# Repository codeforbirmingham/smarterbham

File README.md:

# SmarterBham
The SmarterBham project

# Project Structure
* /citysensor - all the code that runs on the device
* /doc - our documentation.  Requirements, wireframes, flow, security audits, etc
* /web - the web application that we use to manage devices, users, and to analyze collected data

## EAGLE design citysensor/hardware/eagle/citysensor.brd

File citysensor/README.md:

# bham_city_sensor
birmingham city sensor, node implementation

There are some good getting-started details over at http://docs.aws.amazon.com/iot/latest/developerguide/iot-device-sdk-node.html that you should read through before using this.

# setup wifi and AP on the raspberry pi zero w

There's some documentation here on how to setup wifi on the pi:

http://imti.co/post/145442415333/raspberry-pi-3-wifi-station-ap

Note that we are *not* going to bridge the connection between uap0 and wlan0, so
you can use this 'hostapdstart' script instead of the one provided in the tutorial:

```
#!/bin/bash
PATH=/usr/local/sbin:/usr/local/bin:/usr/sbin:/usr/bin:/sbin:/bin
iw dev wlan0 interface add uap0 type __ap
service dnsmasq restart

# comment out these lines to disallow users connected to the
# access point from using the internet connection
#sysctl net.ipv4.ip_forward=1
#iptables -t nat -A POSTROUTING -s 192.168.50.0/24 ! -d 192.168.50.0/24 -j MASQUERADE

ifup uap0
hostapd /etc/hostapd/hostapd.conf
```

Also, you should comment on the following line from /etc/default/hostapd:

```
# commented out to disable hostapd from running on startup,
# since we run this manually in hostapdstart
# DAEMON_CONF="/etc/hostapd/hostapd.conf"
```

# installing node on the raspberry pi zero w

Run scripts/installNode.sh on your Pi device (make it executable).

# checking out the code

```
git clone https://github.com/codeforbirmingham/smarterbham
cd smarterbham/citysensor
```

# configuration

Download your thing certificates from AWS and place them in the certs directory. You will also need the Symantec root certifacate: https://www.symantec.com/content/en/us/enterprise/verisign/roots/VeriSign-Class%203-Public-Primary-Certification-Authority-G5.pem

```
# copy over your aws thing certificates
mkdir certs
cp ~/Downloads/bqqbbg8gaa-certicate.pem.crt certs/
cp ~/Downloads/bqqbbg8gaa-private.pem.key certs/
cp ~/Downloads/bqqbbg8gaa-public.pem.key certs/
curl https://www.symantec.com/content/en/us/enterprise/verisign/roots/VeriSign-Class%203-Public-Primary-Certification-Authority-G5.pem > certs/root-CA.crt
```

You will also need to modify aws_config.js to include information about your thing. You can get this information from the AWS IoT console.

```
{
    "host":           "dw4nbaojaawgawmeba0mdq.iot.us-east-1.amazonaws.com",
    "port":           8883,
    "clientId":       "MyRaspberryPiClient",
    "thingName":      "MyRaspberryPi",
    "caCert":         "root-CA.crt",
    "clientCert":     "bqqbbg8gaa-certificate.pem.crt",
    "privateKey":     "bqqbbg8gaa-private.pem.key"
} 
```

# running within this repo (local development)

```
npm i
npm start
```

This will simulate the web GUI and update the thing's shadow to include new sensor data every so often. You can log into the AWS IoT console and watch the MQTT events for your thing.

# distributing node to run on device (production)

1. Run `npm run dist` to compile app for distribution
2. On your Pi device, we need to run as sudoer to SCP citysensor app from your computer to Pi's local var directory: `sudo scp <username>@<computer ip>:/path/to/smarterbham/citysensor/dist/dist-version.tar.gz /var`
3. On the Pi, navigate to `cd /var` and extract tarball with `sudo tar -xvf dist-version.tar.gz && mv -f dist www`
4. Finally, execute startServer script inside www directory: `sudo ./startServer`

HOST environment variable is *required* to allow server to call itself in the API. This changes based on where the app is deployed and therefore is configured at compile time.

# scripts

There is a control script for the pi in scripts/control.py. You should install this and add the following line to your /etc/rc.local

```
python /path/to/code/scripts/control.py &
```

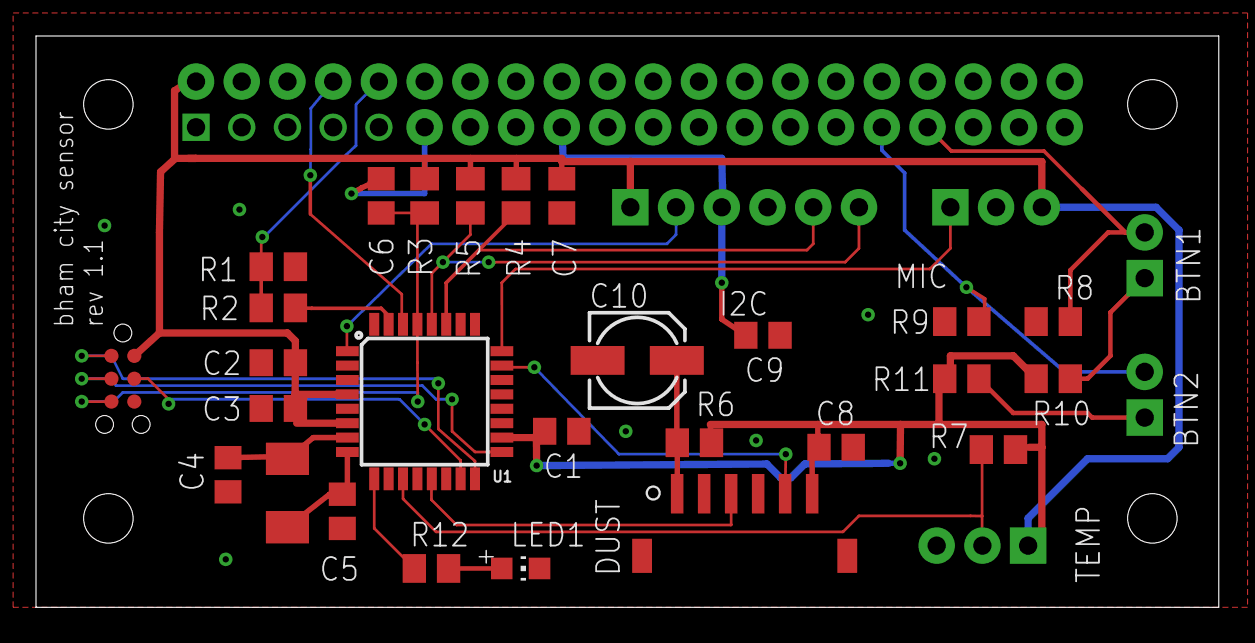
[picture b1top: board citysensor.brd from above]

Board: 2 copper layers, 65.7 x 31.7 mm, 33 parts (0 on the bottom side), 27 nets.

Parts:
BTN1, BTN2: BTN; MOLEX_2
C1, C2, C3, C6, C7, C8, C9: .1uF; C0805
C4, C5: 22pF; C0805
C10: 220uF; 153CLV-0505
DUST: GP2Y1010AU0F; S6B-ZR-SM4A-TF
I2C: CON-I2C; MOLEX_6
LED1: CHIP-LED0805
MIC: MIC; MOLEX_3
R1, R10, R11: 1k; M0805
R2: 510; M0805
R3, R7, R8, R9: 10k; M0805
R4, R5: 4k7; M0805
R6: 150; M0805
R12: 330; M0805
TEMP: DHT11; MOLEX_3
U1: ATMEGA328P_TQFP; TQFP32-08
U$1: PIZERO
U$2: TC2030-CLIP
X1: 16MHZ; CRYSTAL-M445

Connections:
3V3: C9.2, I2C.P$3, U$1.P$17
/RESET: C6.1, R3.1, U1.29, U$2.P$5
ARDTX: R2.2, U1.31
BTN1OUT: BTN1.P$2, R8.1, U$1.P$33
BTN2OUT: BTN2.P$2, R9.1, U$1.P$31
DSTA: DUST.P$5, U1.23
DSTLED: DUST.P$3, U1.13
GND: C1.1, C2.1, C3.1, C4.1, C5.1, C7.2, C8.1, C9.1, C10.-, DUST.P$2, DUST.P$4, I2C.P$4, LED1.C, MIC.P$2, R1.1, R8.2, R9.2, TEMP.P$3, U1.3, U1.5, U1.21, U$1.P$6, U$1.P$9, U$1.P$14, U$1.P$20, U$1.P$25, U$1.P$30, U$1.P$34, U$1.P$39, U$2.P$6
I2C_INT: I2C.P$2, U1.1
MIC_AOUT: MIC.P$1, U1.24
MISO: U1.16, U$2.P$1
MOSI: U1.15, U$2.P$4
unnamed: BTN1.P$1, R10.2
unnamed: BTN2.P$1, R11.2
unnamed: R12.1, U1.9
unnamed: LED1.A, R12.2
unnamed: C4.2, U1.7, X1.P$2
unnamed: C5.2, U1.8, X1.P$1
PIRESET: C6.2, U$1.P$11
PIRX: R1.2, R2.1, U$1.P$10
PITX: U1.30, U$1.P$8
SCK: U1.17, U$2.P$3
SCL: I2C.P$6, R5.2, U1.28
SDA: I2C.P$5, R4.2, U1.27
THDATA: R7.2, TEMP.P$2, U1.11
V-LED: C10.+, DUST.P$1, R6.1
VCC: C1.2, C2.2, C3.2, C7.1, C8.2, DUST.P$6, I2C.P$1, MIC.P$3, R3.2, R4.1, R5.1, R6.2, R7.1, R10.1, R11.1, TEMP.P$1, U1.4, U1.6, U1.18, U$1.P$2, U$2.P$2

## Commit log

2017-08-14 Initial commit
    Moving project from personal repo to CfB repo, restructuring a little so we can also include the docs, web ui stuff, etc
2017-08-14 Added skeleton readme for docs and web
2017-08-15 update readme and add npm script to run node
2017-08-22 reorganized project and added react/webpack boilerplate
2017-08-23 add necessary webpack loaders
2017-08-23 add correct styles and webpack config for toolbox. why is JS so complicated...
2017-09-01 Create LICENSE
2017-09-09 Updated README to include AP / wifi mode instructions
2017-09-09 switched the pi's control script over to the rev1.0 design board
2017-09-09 added some scripts for ap mode
2017-09-09 added /etc/network/interfaces file
2017-09-11 added eagle project file for second generation city sensor, and reorgnized some of the other hardware-related files
2017-09-13 added styles and web fonts along with login page
2017-09-13 move back to original scripts dir
2017-09-14 add the city sensor parts library
2017-09-23 included some more parts into our eagle library
2017-09-24 initial board layout for rev2
2017-09-24 added missing changes to eagle file
2017-09-24 removed ridiculous number of libs in eagle file
2017-09-24 ground-fill the bottom layer
2017-09-24 hooked up reset pin
2017-09-24 added switch locations to eagle file
2017-10-14 added an rgbled component to the city sensor lib. Added a normal led to the board for arduino status
2017-10-14 fixed board labels
2017-12-24 add webpack config and update deps accordingly
2017-12-26 cleaned up project structure and styles views
2017-12-26 add mui theme styles
2017-12-26 clean up unnecessary deps
2017-12-26 add device registration view and protected routes
2017-12-26 add express api for ability to scan for nearby network
2017-12-30 add ref
2017-12-30 connect to wifi and save ap config to file
2017-12-30 create dummy page for device view on successful connection
2018-01-01 added logging middleware
2018-01-01 updated log msg
2018-01-01 fixed ap.json save path
2018-01-01 use sync method
2018-01-01 fix logging for deploys
2018-01-01 load only certain routes based on device status
2018-01-01 load only cdevice home view on successful connection
2018-01-01 add convenience for checking device config and improve registration UX
2018-01-02 improve UX for connecting to secure networks
2018-01-02 update npm commands
2018-01-02 update deps
2018-01-02 clean up. organize logger in utilities dir
2018-01-03 organized routes into own folder
2018-01-03 fix logging path for prod build
2018-01-03 refactor sensor functionality by making it more programmatic
2018-01-03 added sockets for displaying data to web client
2018-01-03 fix table width
2018-01-10 build custom wifi library to support rasberry pi CLI
2018-01-10 remove debug statement
2018-01-10 add connect ability for mac systems
2018-01-10 add notification component
2018-01-14 move project to adopt next.js
2018-01-14 fix routing bugs with next.js
2018-01-14 clean up UX connecting to WIFI
2018-01-14 clean up lint errors
2018-01-14 code cleanup to clarify diff b/t express and next
2018-01-15 rename device api to networks for clarity
2018-01-16 fix vertical alignment issue on registration page
2018-01-20 fix server-rendering material ui issues
2018-01-21 update container propops and main document page
2018-01-21 clean up unnecessary code
2018-01-21 bring in page context to layout
2018-01-22 clean up deps
2018-01-22 make all server side import/export declarations ES5-compatible
2018-01-22 no reason to use babel-cli
2018-01-22 add package tool to deploy app across different systems
2018-01-22 use node paths to determine file locations (pkg support)
2018-01-23 improve dist script for packaging app
2018-01-24 add static assets to dist
2018-01-25 need to take a different path to distribute app to pi
2018-01-25 update logger to be compatible with pi device
2018-01-25 fix lint error
2018-01-25 add device author
2018-01-25 add HOST env var so API works on other servers
2018-01-25 update readme with new node installation instructions
2018-01-25 update readme for distributing app
2018-01-26 allow appropriate watch for files
2018-01-26 fix bug where Pi device can find closed networks
2018-01-26 minor house keeping
2018-01-27 set network on pi device
2018-01-27 organize commands
2018-01-27 correct terminology
2018-02-11 move back to distributing prod app with pkg
2018-02-13 add docker to support arch deployment
2018-02-16 Update package.json
    Fix for reported security vulnerability
2018-02-16 Update package.json
    Updated to 2.2.1 for security fix
2018-02-21 Moved Button connectors away from screw keepout, fixed backwards LED1, rearranged SMD resistors around button connectors. No reported DRC/ERC errors
2018-02-22 update docker deployment
2018-02-23 updated paths and filenames to support pkg dist
2018-02-23 fix lint warnings
2018-03-01 use node 8.9 for docker

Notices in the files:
parts and their libraries:
SparkFun-IC-Microcontroller: Licensing: Creative Commons ShareAlike 4.0 International - https://creativecommons.org/licenses/by-sa/4.0
